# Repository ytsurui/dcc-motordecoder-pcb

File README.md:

# Atmel ATtiny45 DCC Decoder PCB Data

NMRA規格の信号を受信して作動する、モーター駆動専用のDCCデコーダーのDCCデコーダの基板設計データです。

主にNゲージ鉄道模型への搭載を想定して小型に設計してあります。

主要回路についてはすべてディスクリートで構成してあるため、[回路図](docs/schematic.pdf)を参考にして、ブリッジダイオード、MOSFETなどを適宜大電流に対応可能な部品に差し替えることで、より大型のゲージに対応できるデコーダを構成できるかもしれません。

回路図、基板設計データ、面付け済みの設計データを含みます。
<br>面付け済みのデータについては、ガーバーデータも含みます。 (elecrowにて製造できることを確認済み)

### 主要スペック
  * 組み立て後の基板サイズ: 22mm x 10mm x 1.7mm
  * 推奨最大電圧: 16V (搭載する鉄道模型車両の最大電圧以下で使用してください)
  * 出力電流: 最大0.5A
  * コンデンサの搭載や、室内灯電源に対応する+12V / GNDのランドを用意
  * マイコン書き込み用端子を用意し、実装後のプログラム書き換えも可能<br>(AVR ISPのピンを1.27mmピッチで1列に伸ばしています)

### 閲覧・編集に必要なCAD (開発環境)
  * KiCad Version (5.1.6)-1 (またはそれ以降)

### 対応するファームウェア
  * [Atmel ATtiny45 DCC Decoder Firmware](https://github.com/ytsurui/dcc-motordecoder-firmware)

### 各種ドキュメント
  * [パーツリスト](docs/partslist.md)

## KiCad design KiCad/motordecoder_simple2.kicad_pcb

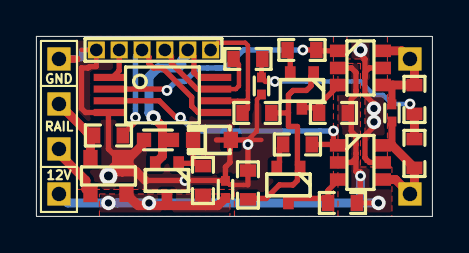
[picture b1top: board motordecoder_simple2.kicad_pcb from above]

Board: 2 copper layers, 22.0 x 10.0 mm, 30 parts (0 on the bottom side), 20 nets.

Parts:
C1, C6, C7: 104; C_1005
C3: 226; C_1608
D1: BAS3007; SOT-143
D3: UDZV5.1B; UMD2
P1, P2, P3, P4, P5, P6: PAD; PAD_1.3x1.3_Hole0.8
P9: PROG; PAD_PROG_6PIN_HOLE0.7
Q1, Q2: DMG6601LVT; SOT-23-6
Q3, Q4, Q5: 2SC4116; SC-70
R1: 104; R_1608
R2, R3, R6, R7, R10: 102; R_1608
R4, R5: 331; R_1608
R8, R9, R11: 103; R_1608
U2: ATtiny45-20SU; TSSOP-8

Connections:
+5V: C3.1, P9.2, Q5.2, U2.8
+12V: C1.1, D1.4, P5.1, Q1.2, Q2.2, Q5.3, R2.1, R3.1, R11.1
BEMF: P9.3, R10.1, U2.7
FUNC1: P9.5, U2.1
FWD: Q2.1, R5.2, U2.3
GND: C1.2, C3.2, C6.2, D1.1, D3.2, P6.1, P9.6, Q1.5, Q2.5, R7.2, U2.4
MOSI: P9.4, R1.1, U2.5
MOTOR+: C7.1, P3.1, Q1.4, Q1.6, R8.2
MOTOR-: C7.2, P4.1, Q2.4, Q2.6, R9.2
unnamed: C6.1, R8.1, R9.1, R10.2
unnamed: D3.1, Q5.1, R11.2
unnamed: Q1.3, Q3.3, R2.2
unnamed: Q2.3, Q4.3, R3.2
unnamed: Q3.1, Q4.1, R6.2, R7.1
unnamed: Q3.2, R4.1
unnamed: Q4.2, R5.1
PWM: P9.1, R6.1, U2.6
RAIL+: D1.2, P1.1, R1.2
RAIL-: D1.3, P2.1
REV: Q1.1, R4.2, U2.2
